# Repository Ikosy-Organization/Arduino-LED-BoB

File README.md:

# Arduino-LED-BoB

A PCB for Arduino testing.  Makes setting up 4 LEDs very easy.

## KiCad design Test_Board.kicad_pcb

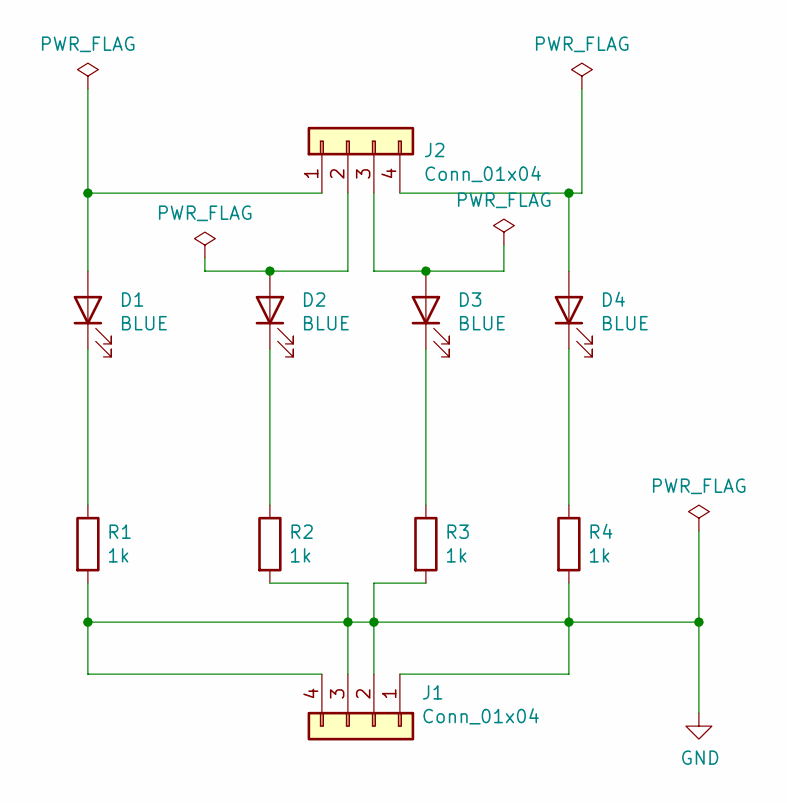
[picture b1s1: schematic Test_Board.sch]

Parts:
D1, D2, D3, D4: BLUE; D_0805_2012Metric; Manufacturer Part # 150080BS75000
J1: Conn_01x04; PinHeader_1x04_P2.54mm_Vertical; Manufacturer Part # 68000-404HLF
J2: Conn_01x04; Input_PinHeader_1x04_P2.54mm_Vertical; Manufacturer Part # 68000-404HLF
R1, R2, R3, R4: 1k; R_0603_1608Metric; Manufacturer Part # ESR03EZPF1001

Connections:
GND: J1.1, J1.2, J1.3, J1.4, R1.2, R2.2, R3.2, R4.2
unnamed: D1.1 (K), R1.1
unnamed: D1.2 (A), J2.1
unnamed: D2.1 (K), R2.1
unnamed: D2.2 (A), J2.2
unnamed: D3.1 (K), R3.1
unnamed: D3.2 (A), J2.3
unnamed: D4.1 (K), R4.1
unnamed: D4.2 (A), J2.4

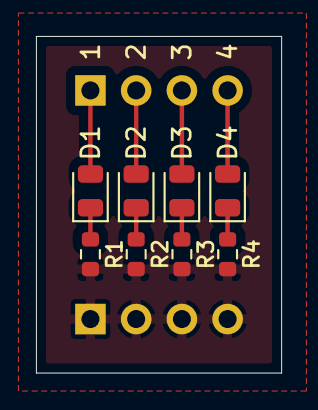
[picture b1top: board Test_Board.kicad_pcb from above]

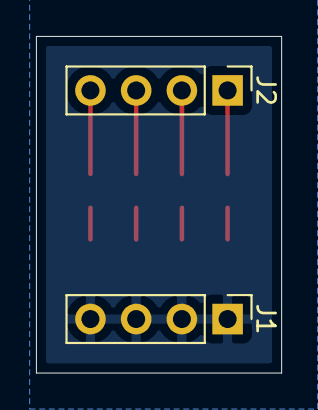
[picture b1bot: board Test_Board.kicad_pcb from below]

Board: 2 copper layers, 13.6 x 18.7 mm, 10 parts (2 on the bottom side), 9 nets.
